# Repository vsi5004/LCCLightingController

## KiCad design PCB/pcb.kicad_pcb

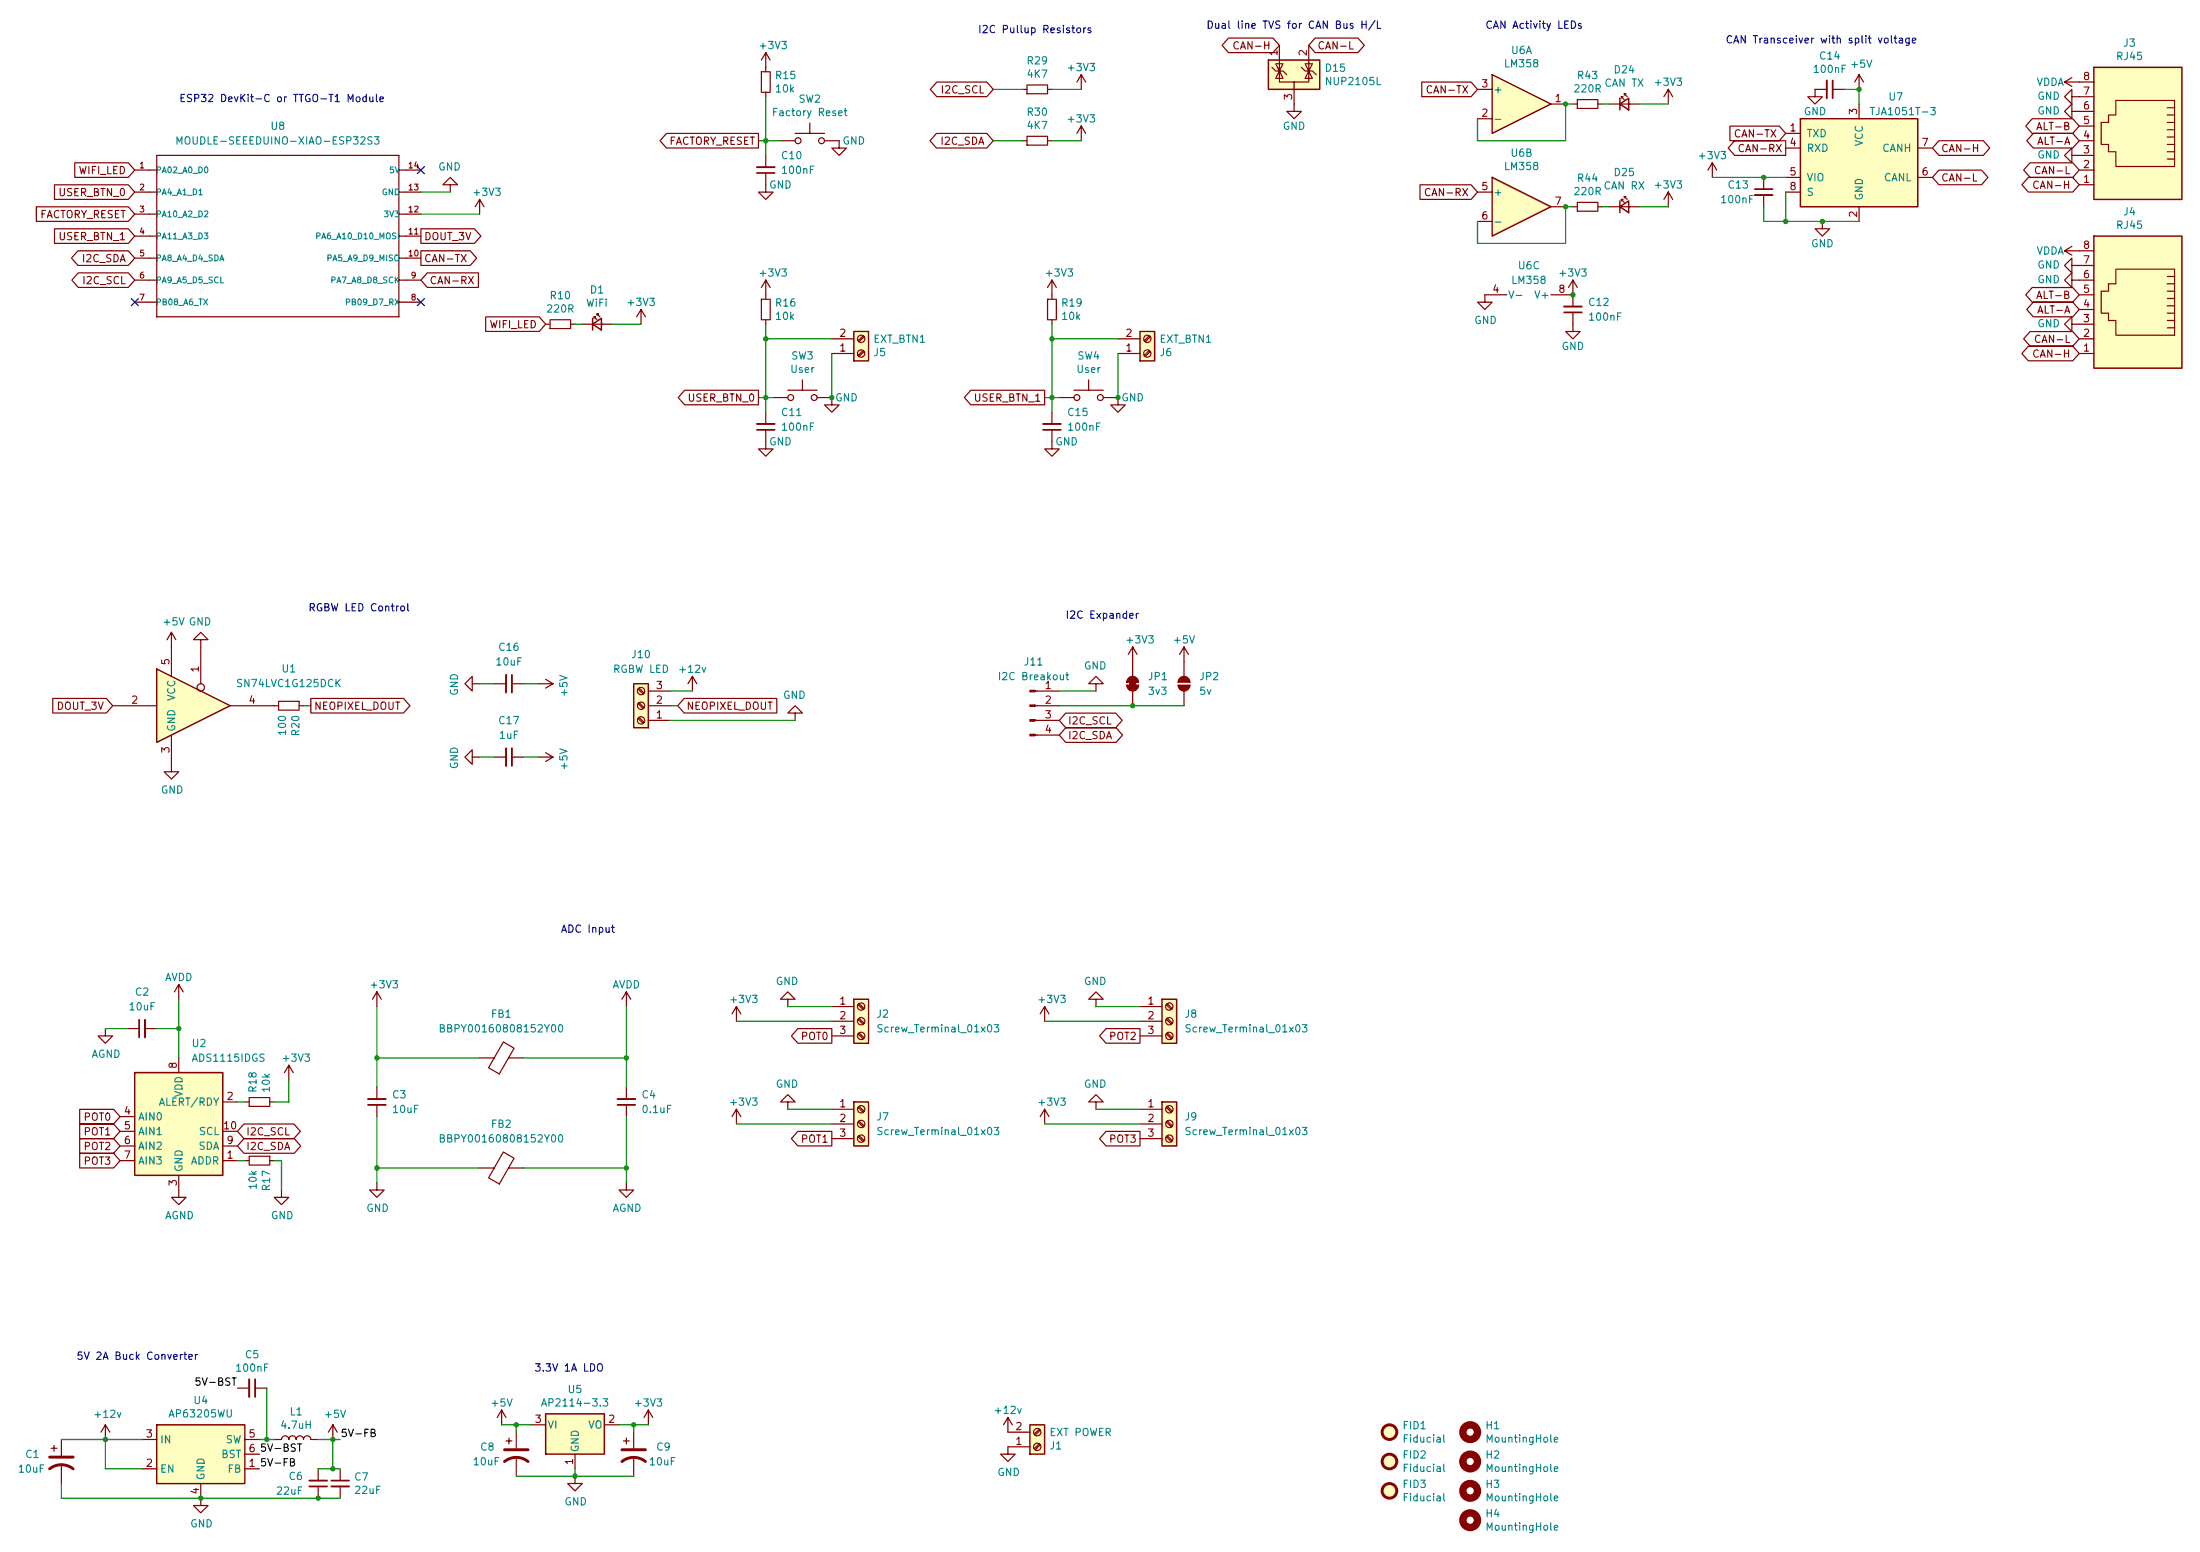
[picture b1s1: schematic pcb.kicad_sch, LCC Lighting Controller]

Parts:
C1, C8, C9: 10uF; CP_Elec_5x5.3; Mouser 710-865230542002
C2, C3, C16: 10uF; C_0805_2012Metric_Pad1.18x1.45mm_HandSolder
C4: 0.1uF; C_0805_2012Metric_Pad1.18x1.45mm_HandSolder
C5, C10, C11, C12, C13, C14, C15: 100nF; C_0603_1608Metric; Mouser 710-885012206020
C6, C7: 22uF; C_0603_1608Metric; Mouser 603-CC0603MRX6S5B226
C17: 1uF; C_0805_2012Metric_Pad1.18x1.45mm_HandSolder
D1: WiFi; LED_0603_1608Metric; Mouser 710-150060VS55040
D15: NUP2105L; SOT-23; Mouser 863-SZNUP2105LT3G
D24: CAN TX; LED_0603_1608Metric; Mouser 710-150060YS75000
D25: CAN RX; LED_0603_1608Metric; Mouser 710-150060AS75000
FB1, FB2: BBPY00160808152Y00; L_0603_1608Metric_Pad1.05x0.95mm_HandSolder
FID1, FID2, FID3: Fiducial; Fiducial_0.5mm_Mask1mm
H1, H2, H3, H4: MountingHole; MountingHole_3.2mm_M3_Pad
J1: EXT POWER; TerminalBlock_Phoenix_PT-1,5-2-3.5-H_1x02_P3.50mm_Horizontal; Mouser 651-1984617
J2, J7, J8, J9: Screw_Terminal_01x03; TerminalBlock_Phoenix_PT-1,5-3-3.5-H_1x03_P3.50mm_Horizontal
J3, J4: RJ45; RJ45_TE_CONNECTIVITY_5555164-1_Horizontal-Low_Profile; Mouser 571-5569284-1 or 534-949 or 493-HCJV1-8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
J5, J6: EXT_BTN1; TerminalBlock_Phoenix_PT-1,5-2-3.5-H_1x02_P3.50mm_Horizontal; Mouser 651-1984617
J10: RGBW LED; TerminalBlock_Phoenix_PT-1,5-3-3.5-H_1x03_P3.50mm_Horizontal
J11: I2C Breakout; PinSocket_1x04_P2.54mm_Vertical
JP1: 3v3; SolderJumper-2_P1.3mm_Bridged_RoundedPad1.0x1.5mm
JP2: 5v; SolderJumper-2_P1.3mm_Open_RoundedPad1.0x1.5mm
L1: 4.7uH; IND_B1047AS-4R7N=P3; Mouser 81-B1047AS-4R7NP3
R10, R43, R44: 220R; R_0603_1608Metric; Mouser 603-AC0603JR-07160RL
R15, R16, R17, R18, R19: 10k; R_0603_1608Metric; Mouser 71-CRCW06030000Z0EAC
R20: 100; R_0603_1608Metric; Mouser 71-CRCW06030000Z0EAC
R29, R30: 4K7; R_0603_1608Metric; Mouser 603-AC0603JR-07160RL
SW2: Factory Reset; SW_Tactile_SPST_NO_Straight_CK_PTS636Sx25SMTRLFS; Mouser 667-EVQ-PE104K
SW3, SW4: User; SW_Tactile_SPST_NO_Straight_CK_PTS636Sx25SMTRLFS; Mouser 667-EVQ-PE104K
U1: SN74LVC1G125DCK; Texas_R-PDSO-G5_DCK-5
U2: ADS1115IDGS; TSSOP-10_3x3mm_P0.5mm
U4: AP63205WU; TSOT-23-6; Mouser 621-AP63205WU-7
U5: AP2114-3.3; SOT-223-3_TabPin2; Mouser 621-AP2114H-3.3TRG1
U6: LM358; SOIC-8_3.9x4.9mm_P1.27mm; Mouser 595-LM358BIDR
U7: TJA1051T-3; SOIC-8_3.9x4.9mm_P1.27mm; Mouser 726-IFX1050GVIOXUMA1
U8: MOUDLE-SEEEDUINO-XIAO-ESP32S3; MCU_Seeed_ESP32C3_TH

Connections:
+3V3: C3.2, C9.1, C12.2, C13.1, D1.2 (A), D24.2 (A), D25.2 (A), FB1.1, J2.2, J7.2, J8.2, J9.2, JP1.2 (B), R15.1, R16.1, R18.2, R19.1, R29.2, R30.2, U5.2 (VO), U6.8 (V+), U7.5 (VIO), U8.12 (3V3)
+5V: C6.2, C7.1, C8.1, C14.1, C16.1, C17.1, JP2.2 (B), L1.2, U1.5 (VCC), U4.1 (FB), U5.3 (VI), U7.3 (VCC)
+12v: C1.1, J1.2, J10.3, U4.2 (EN), U4.3 (IN)
/5V-BST: C5.2, U4.6 (BST)
AGND: C2.1, C4.1, FB2.2, U2.3 (GND)
ALT-A: J3.4, J4.4
ALT-B: J3.5, J4.5
AVDD: C2.2, C4.2, FB1.2, U2.8 (VDD)
CAN-H: D15.1 (K), J3.1, J4.1, U7.7 (CANH)
CAN-L: D15.2 (K), J3.2, J4.2, U7.6 (CANL)
CAN-RX: U6.5 (+), U7.4 (RXD), U8.9 (PA7_A8_D8_SCK)
CAN-TX: U6.3 (+), U7.1 (TXD), U8.10 (PA5_A9_D9_MISO)
DOUT_3V: U1.2, U8.11 (PA6_A10_D10_MOSI)
FACTORY_RESET: C10.2, R15.2, SW2.1, U8.3 (PA10_A2_D2)
GND: C1.2, C3.1, C6.1, C7.2, C8.2, C9.2, C10.1, C11.1, C12.1, C13.2, C14.2, C15.1, C16.2, C17.2, D15.3 (A), FB2.1, J1.1, J2.1, J3.3, J3.6, J3.7, J4.3, J4.6, J4.7, J5.1, J6.1, J7.1, J8.1, J9.1, J10.1, J11.1, R17.1, SW2.2, SW3.2, SW4.2, U1.1, U1.3 (GND), U4.4 (GND), U5.1 (GND), U6.4 (V-), U7.2 (GND), U7.8 (S), U8.13 (GND)
I2C_SCL: J11.3, R29.1, U2.10 (SCL), U8.6 (PA9_A5_D5_SCL)
I2C_SDA: J11.4, R30.1, U2.9 (SDA), U8.5 (PA8_A4_D4_SDA)
NEOPIXEL_DOUT: J10.2, R20.1
unnamed: D1.1 (K), R10.2
unnamed: D24.1 (K), R43.2
unnamed: D25.1 (K), R44.2
unnamed: J11.2, JP1.1 (A), JP2.1 (A)
unnamed: R20.2, U1.4
unnamed: R17.2, U2.1 (ADDR)
unnamed: R18.1, U2.2 (ALERT/RDY)
unnamed: C5.1, L1.1, U4.5 (SW)
unnamed: R43.1, U6.1, U6.2 (-)
unnamed: R44.1, U6.6 (-), U6.7
POT0: J2.3, U2.4 (AIN0)
POT1: J7.3, U2.5 (AIN1)
POT2: J8.3, U2.6 (AIN2)
POT3: J9.3, U2.7 (AIN3)
USER_BTN_0: C11.2, J5.2, R16.2, SW3.1, U8.2 (PA4_A1_D1)
USER_BTN_1: C15.2, J6.2, R19.2, SW4.1, U8.4 (PA11_A3_D3)
VDDA: J3.8, J4.8
WIFI_LED: R10.1, U8.1 (PA02_A0_D0)

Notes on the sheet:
I2C Pullup Resistors
5V 2A Buck Converter
3.3V 1A LDO
ESP32 DevKit-C or TTGO-T1 Module
CAN Transceiver with split voltage
RGBW LED Control
I2C Expander
ADC Input
CAN Activity LEDs
Dual line TVS for CAN Bus H/L

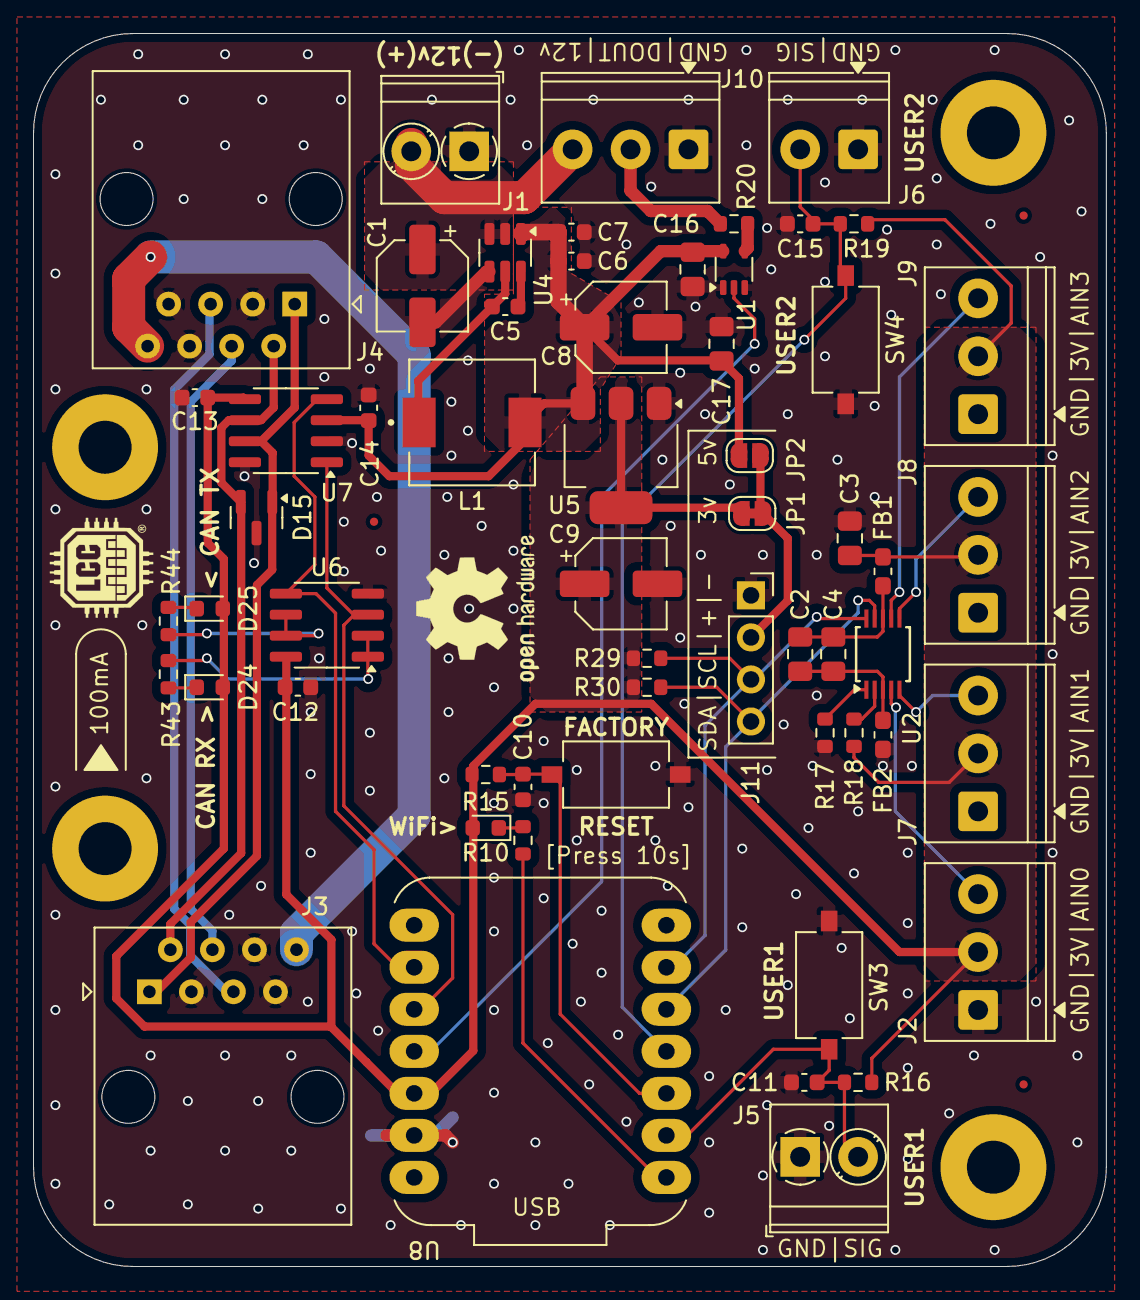
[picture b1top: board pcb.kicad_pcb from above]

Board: 2 copper layers, 64.8 x 74.5 mm, 65 parts (0 on the bottom side), 36 nets.

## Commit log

2025-04-25 Add PCB files
2025-11-26 Initial commit bringing FW over from LCC Turnout Controller
2025-11-26 FW works on coordinating device but does not support LCC communication
2025-11-27 Update to send/receive single message per lighting parameter, fix event ID bug
2025-11-28 Add startup animation, fix bugs with event mask filter
2025-11-29 Update NODE_ID, add sync interval configuration, and implement periodic sync for RGBW controller
2026-01-13 Add startup delay configuration and implement fade-in animation for RGBW controller
2026-01-13 PR Changes
2026-01-13 Initial firmware implementation (#1)
    * Initial commit bringing FW over from LCC Turnout Controller
    * FW works on coordinating device but does not support LCC communication
    * Update to send/receive single message per lighting parameter, fix event ID bug
    * Add startup animation, fix bugs with event mask filter
    * Update NODE_ID, add sync interval configuration, and implement periodic sync for RGBW controller
    * Add startup delay configuration and implement fade-in animation for RGBW controller
2026-01-15 Update PCB files with latest rev, export fabrication outputs, update README and add documentation photos
2026-01-21 Update to use new transition duration protocol, add factory reset button functionality, update neopixel driver to use DMA library
